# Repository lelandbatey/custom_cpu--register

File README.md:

CPU Register
============

This repo contains PCB designs for the second component of Ben Eater's
educational 8-bit CPU, the CPU registers. You can [watch Mr. Eaters *fantastic*
series on designing and building this CPU on his Youtube
channel.](https://www.youtube.com/user/eaterbc/videos)

Each CPU will need three of these registers, one to act as the **instruction**
register, one as the **A** register, and one as the **B** register. The
difference between the A/B registers and the instruction register is that the
four most significant bits of the instruction register won't be directed back
onto the bus, but instead are used as input to the instruction decoder. The
design intentionally incorporates fake resistors in between the LED's and the
LS74245 which may be used as the point where those four most significant bits
are split off towards the instruction decoder.

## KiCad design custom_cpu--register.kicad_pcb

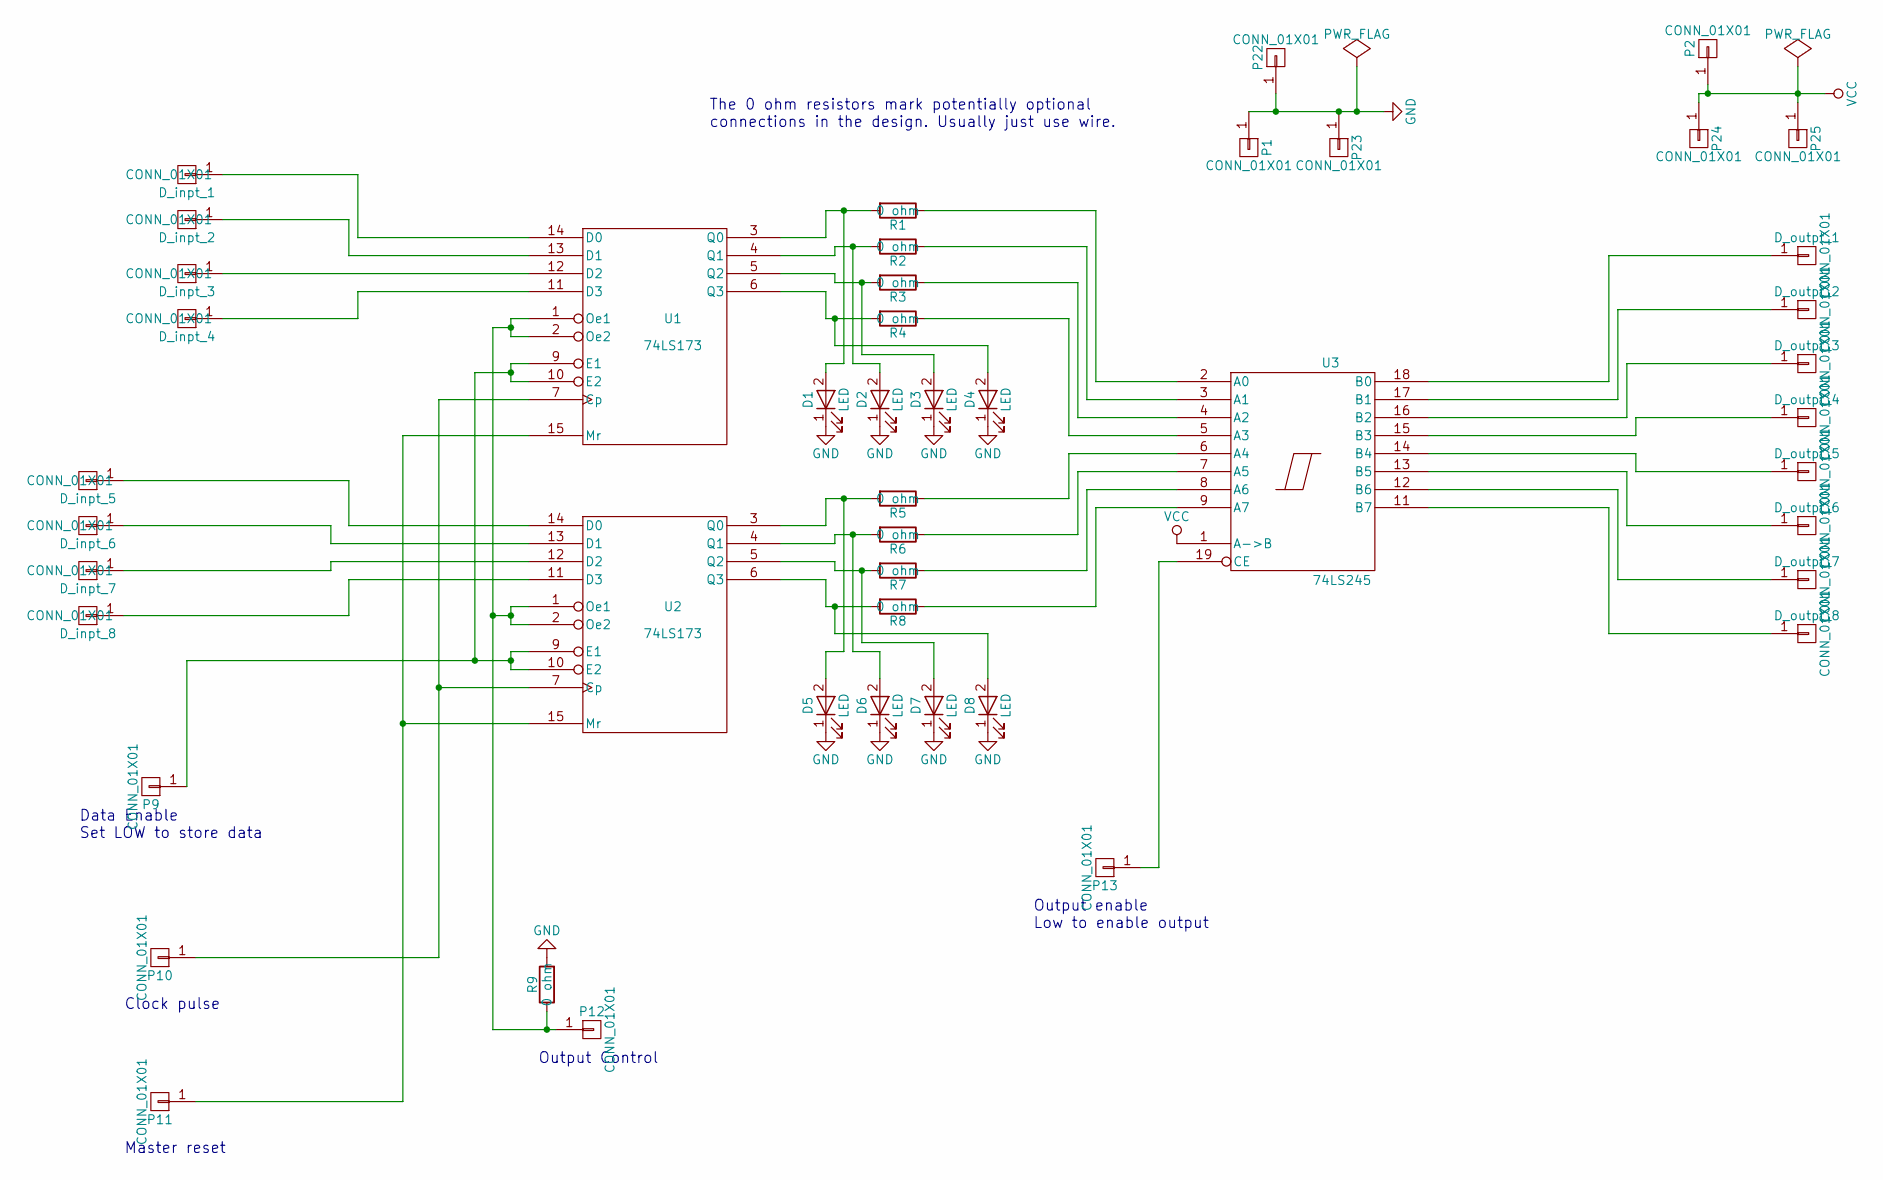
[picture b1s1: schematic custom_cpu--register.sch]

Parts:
D1, D2, D3, D4, D5, D6, D7, D8: LED; LED_D5.0mm
D_inpt_1, D_inpt_2, D_inpt_3, D_inpt_4, D_inpt_5, D_inpt_6, D_inpt_7, D_inpt_8: CONN_01X01; PINTST
D_outpt_1, D_outpt_2, D_outpt_3, D_outpt_4, D_outpt_5, D_outpt_6, D_outpt_7, D_outpt_8: CONN_01X01; PINTST
P1, P2, P23, P25: CONN_01X01; SolderWirePad_single_SMD_5x10mm
P9, P10, P11, P12, P13, P22, P24: CONN_01X01; PINTST
R1, R2, R3, R4, R5, R6, R7, R8, R9: 0 ohm; R_Axial_DIN0204_L3.6mm_D1.6mm_P7.62mm_Horizontal
U1, U2: 74LS173; DIP-16_W7.62mm_Socket
U3: 74LS245; DIP-20_W7.62mm_Socket

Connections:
GND: D1.1 (K), D2.1 (K), D3.1 (K), D4.1 (K), D5.1 (K), D6.1 (K), D7.1 (K), D8.1 (K), P1.1, P22.1, P23.1, R9.2, U1.8 (GND), U2.8 (GND), U3.10 (GND)
unnamed: D1.2 (A), R1.2, U1.3 (Q0)
unnamed: D2.2 (A), R2.2, U1.4 (Q1)
unnamed: D3.2 (A), R3.2, U1.5 (Q2)
unnamed: D4.2 (A), R4.2, U1.6 (Q3)
unnamed: D5.2 (A), R5.2, U2.3 (Q0)
unnamed: D6.2 (A), R6.2, U2.4 (Q1)
unnamed: D7.2 (A), R7.2, U2.5 (Q2)
unnamed: D8.2 (A), R8.2, U2.6 (Q3)
unnamed: D_inpt_1.1, U1.14 (D0)
unnamed: D_inpt_2.1, U1.13 (D1)
unnamed: D_inpt_3.1, U1.12 (D2)
unnamed: D_inpt_4.1, U1.11 (D3)
unnamed: D_inpt_5.1, U2.14 (D0)
unnamed: D_inpt_6.1, U2.13 (D1)
unnamed: D_inpt_7.1, U2.12 (D2)
unnamed: D_inpt_8.1, U2.11 (D3)
unnamed: D_outpt_1.1, U3.18 (B0)
unnamed: D_outpt_2.1, U3.17 (B1)
unnamed: D_outpt_3.1, U3.16 (B2)
unnamed: D_outpt_4.1, U3.15 (B3)
unnamed: D_outpt_5.1, U3.14 (B4)
unnamed: D_outpt_6.1, U3.13 (B5)
unnamed: D_outpt_7.1, U3.12 (B6)
unnamed: D_outpt_8.1, U3.11 (B7)
unnamed: P9.1, U1.9 (E1), U1.10 (E2), U2.9 (E1), U2.10 (E2)
unnamed: P10.1, U1.7 (Cp), U2.7 (Cp)
unnamed: P11.1, U1.15 (Mr), U2.15 (Mr)
unnamed: P12.1, R9.1, U1.1 (Oe1), U1.2 (Oe2), U2.1 (Oe1), U2.2 (Oe2)
unnamed: P13.1, U3.19 (CE)
unnamed: R1.1, U3.2 (A0)
unnamed: R2.1, U3.3 (A1)
unnamed: R3.1, U3.4 (A2)
unnamed: R4.1, U3.5 (A3)
unnamed: R5.1, U3.6 (A4)
unnamed: R6.1, U3.7 (A5)
unnamed: R7.1, U3.8 (A6)
unnamed: R8.1, U3.9 (A7)
VCC: P2.1, P24.1, P25.1, U1.16 (VCC), U2.16 (VCC), U3.1 (A->B), U3.20 (VCC)

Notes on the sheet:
Data Enable Set LOW to store data
Clock pulse
Master reset
Output Control
Output enable Low to enable output
The 0 ohm resistors mark potentially optional connections in the design. Usually just use wire.

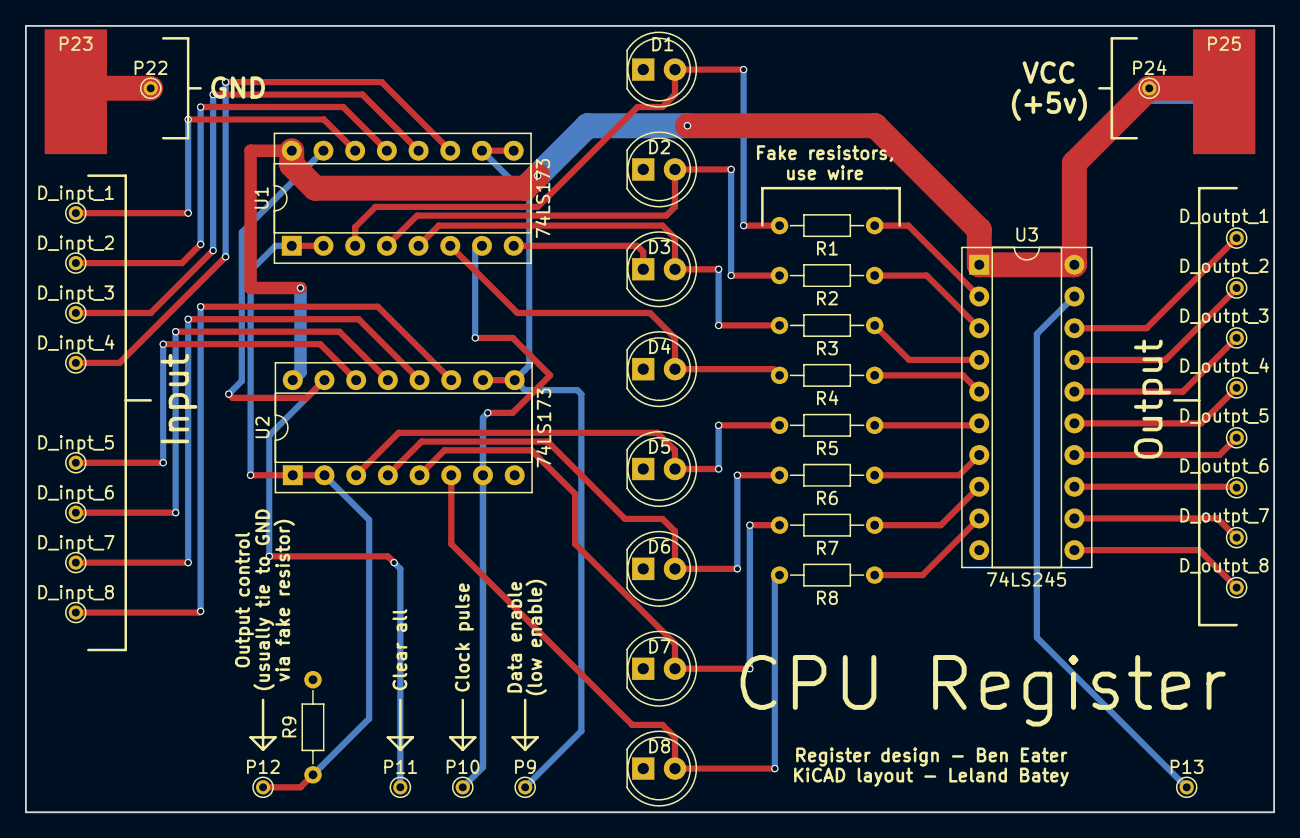
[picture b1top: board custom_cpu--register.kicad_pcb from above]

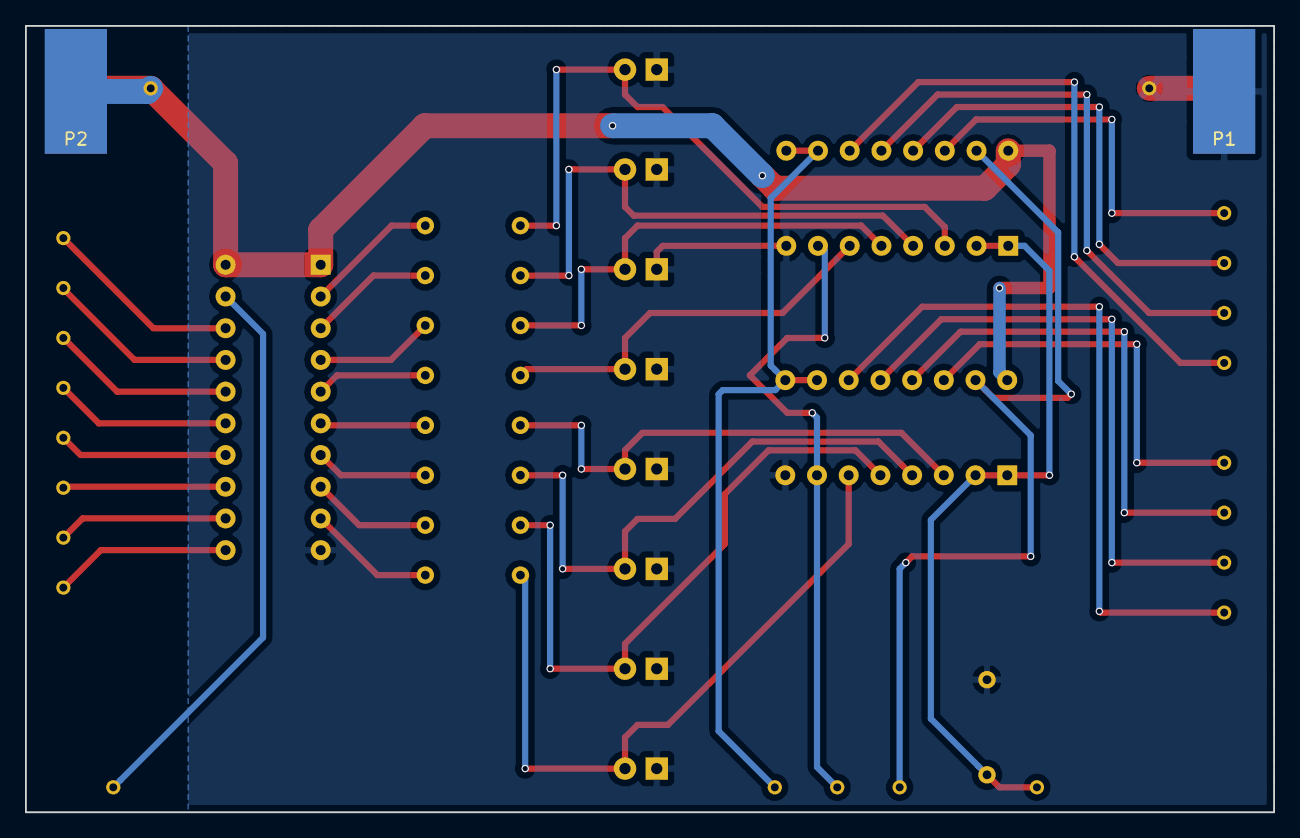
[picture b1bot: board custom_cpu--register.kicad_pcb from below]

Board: 2 copper layers, 100.0 x 63.0 mm, 47 parts (2 on the bottom side), 39 nets.

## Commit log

2017-04-08 Finish preliminary design
2017-04-09 Tweak trace layout, add PNG version of layout
2017-04-09 Make labels consistent with original design, add README
2017-04-09 Added redundant power pads to back of board
2017-04-09 Add output control label
2017-06-03 Add parts list and cost of materials
